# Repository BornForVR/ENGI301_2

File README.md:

# Project 2: PCB Design for Simplified Assembly

## Overview
This project is an extension of Project 1, where we developed a system using a PocketBeagle to control various peripherals. The goal of Project 2 is to streamline the assembly process by creating a dedicated PCB, which reduces the complexity of wiring and provides a hands-on experience in PCB design.

## Features
- **Female Pin Connectors**: For easy connection to the display and rotary encoder.
- **Male Connectors**: To connect two stepper motor drive boards.
- **Simplified Wiring**: Reduces the clutter and potential errors associated with manual wiring.

### Installing
A step-by-step series of examples that tell you how to get a development environment running:

- Clone the repo to your local machine.
- Ensure you have a suitable PCB fabricator ready to produce the board.
- Gather all necessary components as listed in the documentation.

- ## Usage

Solder the headers to the PCB as indicated in the design files.
Attach the display and rotary encoder to the female connectors.
Connect the stepper motors to the male connectors.
Connect the PocketBeagle according to the schematic provided.

## Built With
- **Eagle PCB Design Software** - Used to create the PCB layout.

## Acknowledgments
We extend our deepest gratitude to Professor Erik Welsh, our esteemed instructor for ENGI 301, whose guidance and expertise were invaluable throughout the course of this project.

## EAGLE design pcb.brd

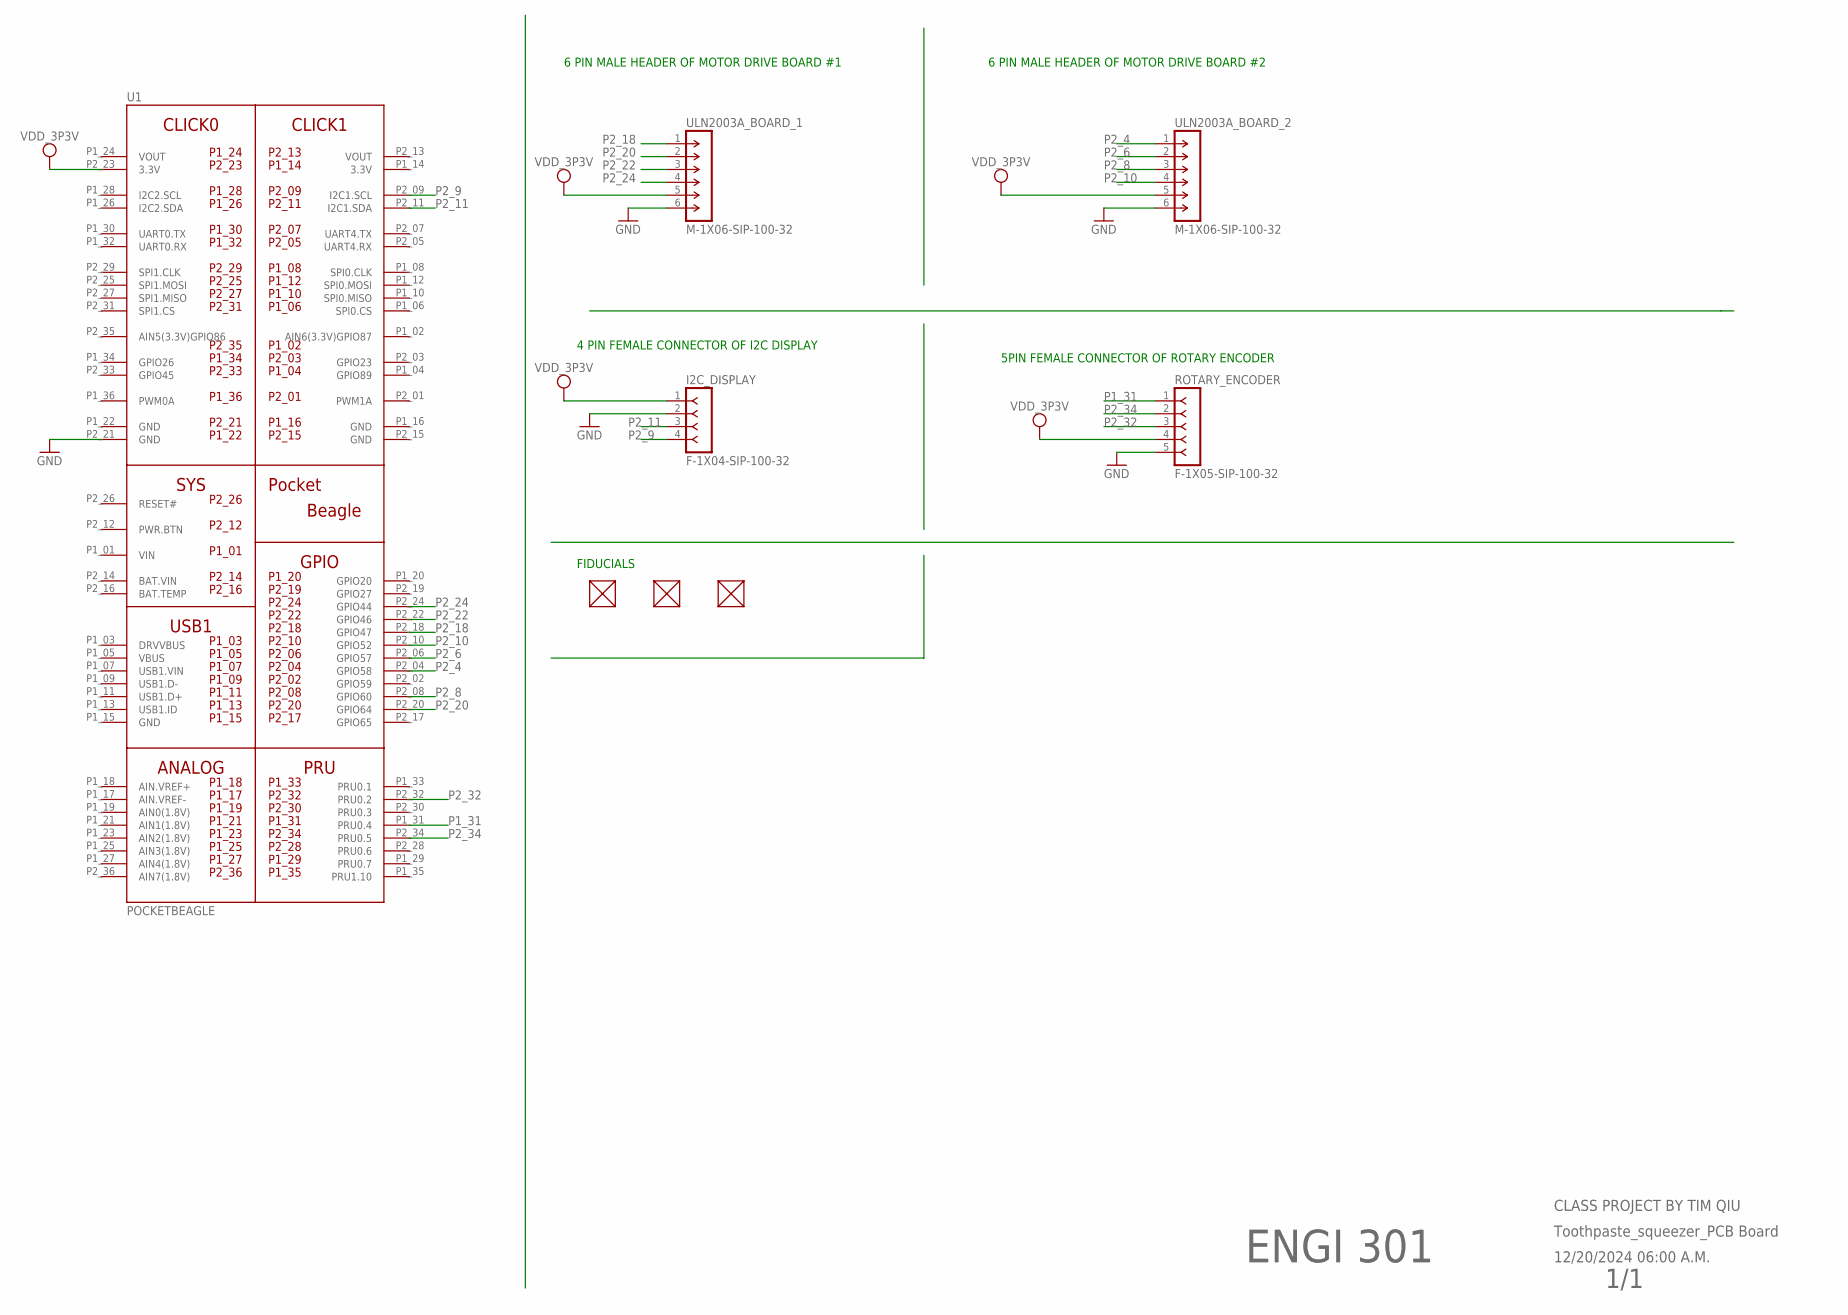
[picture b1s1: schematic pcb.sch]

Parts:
FUD1, FUD2, FUD3: FIDUCIAL; FIDUCIAL_40MIL
I2C_DISPLAY: F-1X04-SIP-100-32; SIP-100-04-32
ROTARY_ENCODER: F-1X05-SIP-100-32; SIP-100-05-32
U1: POCKETBEAGLE
ULN2003A_BOARD_1, ULN2003A_BOARD_2: M-1X06-SIP-100-32; SIP-100-06-32

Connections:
3.3V: U1.P1_14 (3.3V)
BAT.VIN: U1.P2_14 (BAT.VIN)
GND: I2C_DISPLAY.2, ROTARY_ENCODER.5, U1.P1_16 (GND), U1.P1_22 (GND), U1.P2_15 (GND), U1.P2_21 (GND), ULN2003A_BOARD_1.6, ULN2003A_BOARD_2.6
P1_31: ROTARY_ENCODER.1, U1.P1_31 (PRU0.4)
P2_4: U1.P2_04 (GPIO58), ULN2003A_BOARD_2.1
P2_6: U1.P2_06 (GPIO57), ULN2003A_BOARD_2.2
P2_8: U1.P2_08 (GPIO60), ULN2003A_BOARD_2.3
P2_9: I2C_DISPLAY.4, U1.P2_09 (I2C1.SCL)
P2_10: U1.P2_10 (GPIO52), ULN2003A_BOARD_2.4
P2_11: I2C_DISPLAY.3, U1.P2_11 (I2C1.SDA)
P2_18: U1.P2_18 (GPIO47), ULN2003A_BOARD_1.1
P2_20: U1.P2_20 (GPIO64), ULN2003A_BOARD_1.2
P2_22: U1.P2_22 (GPIO46), ULN2003A_BOARD_1.3
P2_24: U1.P2_24 (GPIO44), ULN2003A_BOARD_1.4
P2_32: ROTARY_ENCODER.3, U1.P2_32 (PRU0.2)
P2_34: ROTARY_ENCODER.2, U1.P2_34 (PRU0.5)
VDD_3P3V: I2C_DISPLAY.1, ROTARY_ENCODER.4, U1.P2_23 (3.3V), ULN2003A_BOARD_1.5, ULN2003A_BOARD_2.5
VIN: U1.P1_01 (VIN)
VOUT: U1.P1_24 (VOUT), U1.P2_13 (VOUT)

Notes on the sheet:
6 PIN MALE HEADER OF MOTOR DRIVE BOARD #1
6 PIN MALE HEADER OF MOTOR DRIVE BOARD #2
4 PIN FEMALE CONNECTOR OF I2C DISPLAY
5PIN FEMALE CONNECTOR OF ROTARY ENCODER
ENGI 301
1/1
CLASS PROJECT BY TIM QIU
Toothpaste_squeezer_PCB Board
12/20/2024 06:00 A.M.
FIDUCIALS

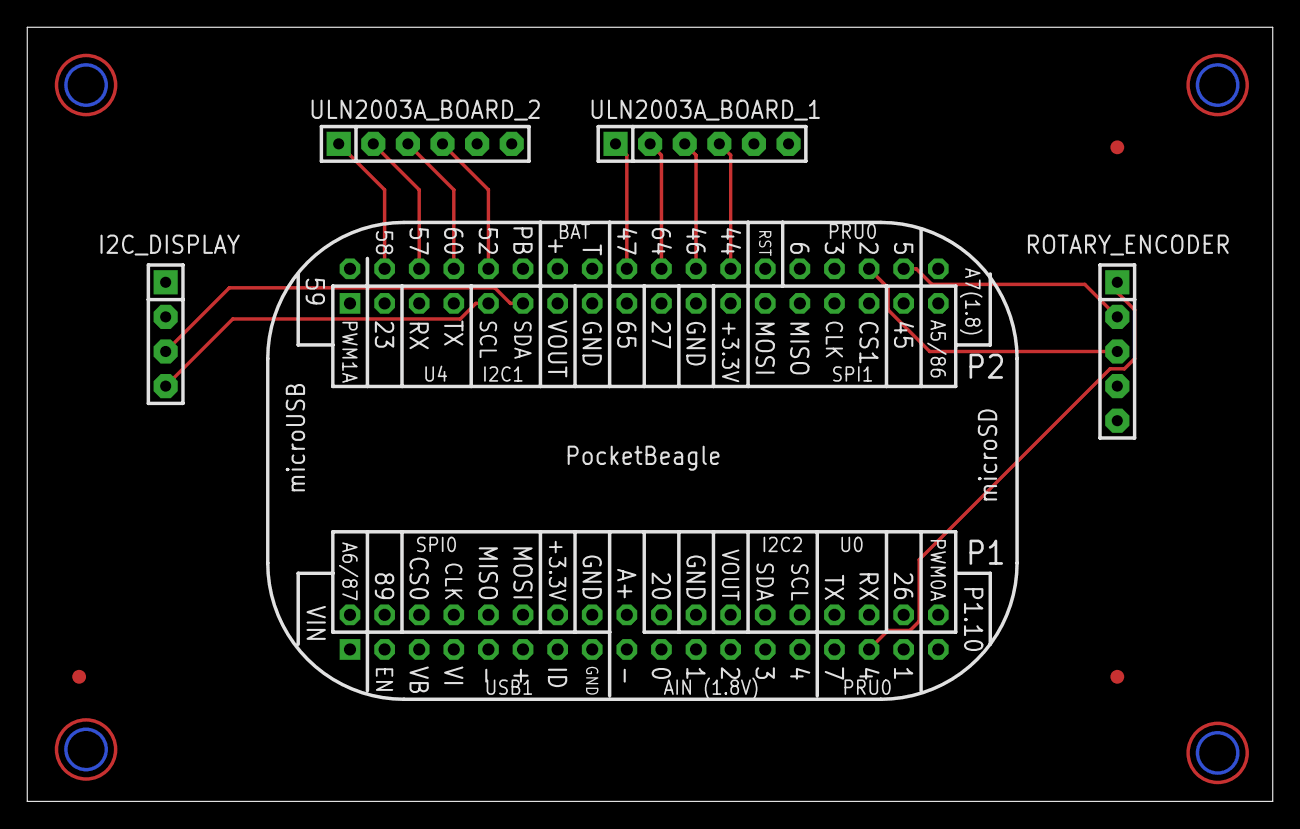
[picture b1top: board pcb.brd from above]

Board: 4 copper layers, 91.4 x 56.8 mm, 8 parts (0 on the bottom side), 16 nets.

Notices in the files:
parts and their libraries:
con-headers-jp: Copyright (C) 2008, Bob Starr
